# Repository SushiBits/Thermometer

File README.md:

# Thermocople Terminal

This is a thermocouple thermometer. Its USB link allows you to connect it to a
computer or a Raspberry Pi to log its output data.

For the matching firmware project, please visit [here](https://github.com/SushiBits/Thermocouple-firmware).

## License and more

This is open source hardware under [3-clause BSD license](LICENSE.md). You are
encouraged to modify and provide feedback.

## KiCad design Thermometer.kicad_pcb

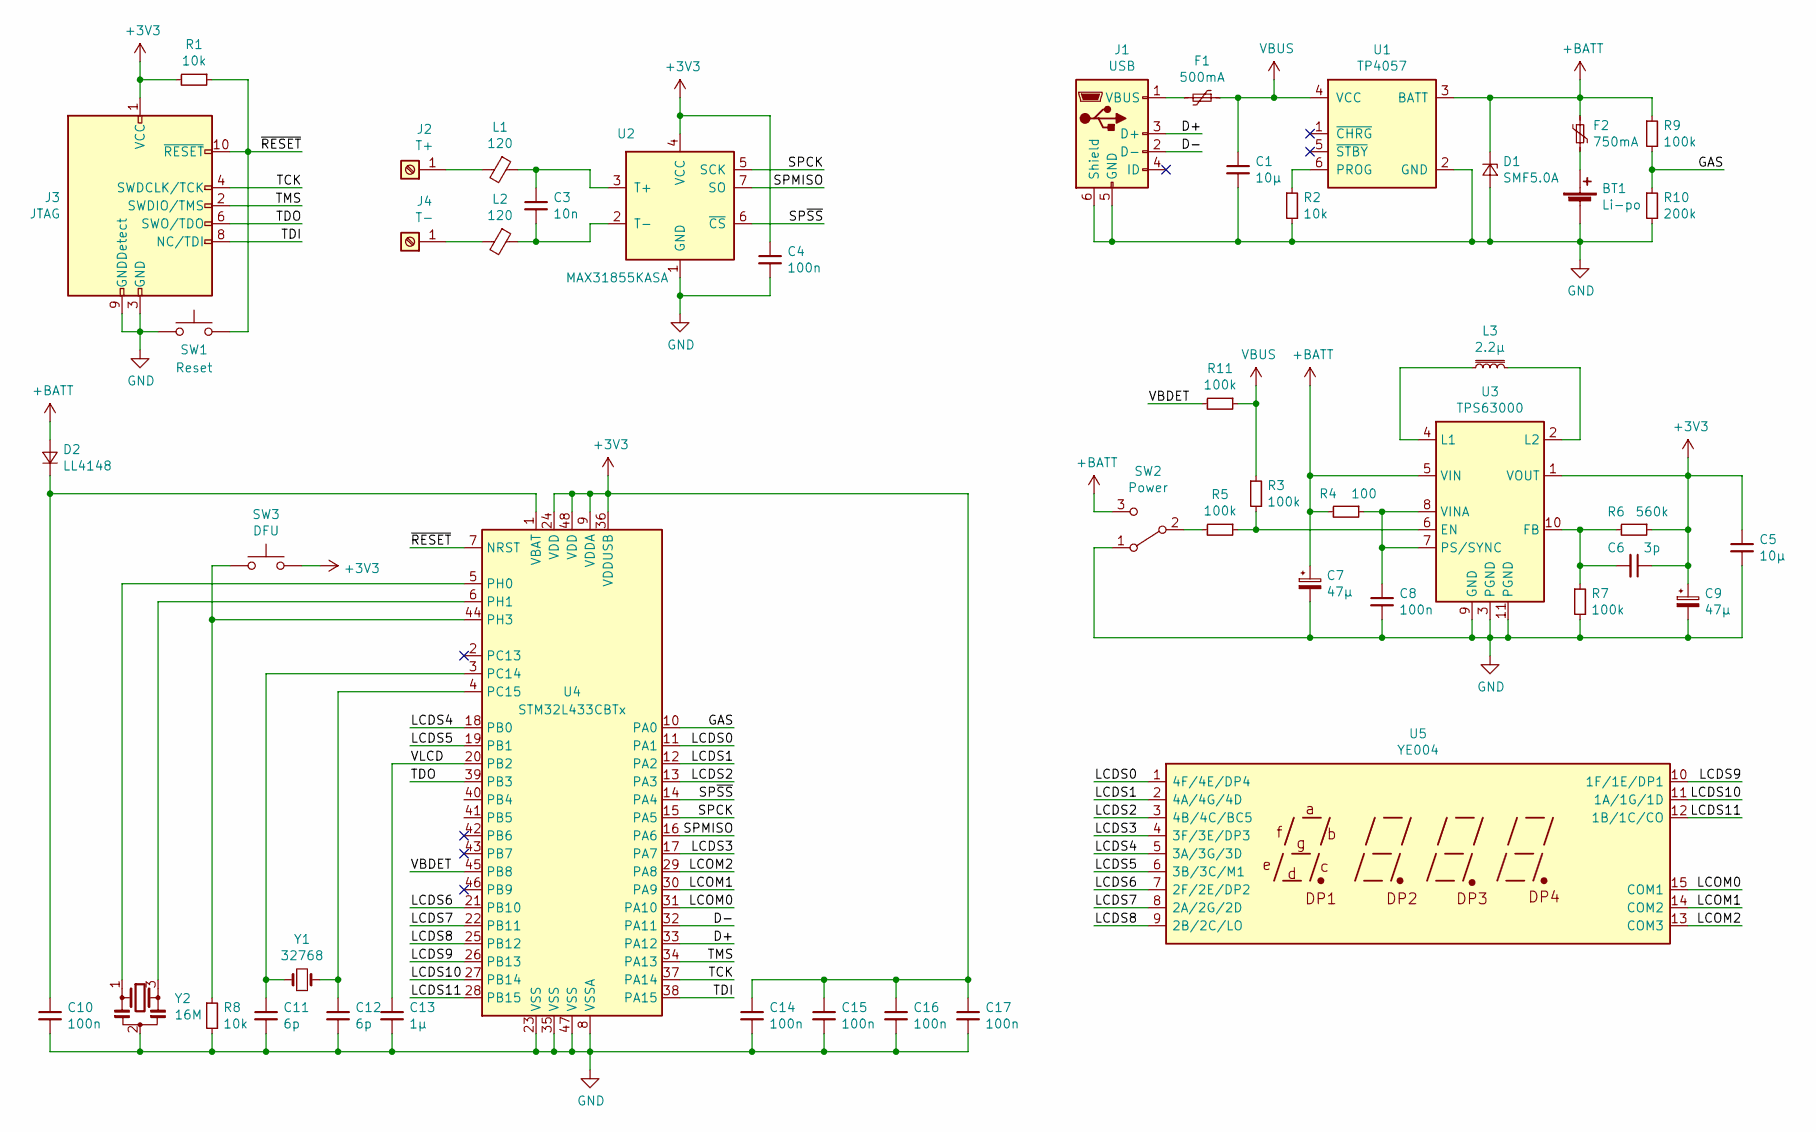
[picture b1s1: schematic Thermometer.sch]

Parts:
BT1: Li-po; PinHeader_1x02_P1.27mm_Vertical
C1, C5: 10µ; C_0805_2012Metric_Pad1.15x1.40mm_HandSolder
C3: 10n; C_0603_1608Metric_Pad1.05x0.95mm_HandSolder
C4, C8, C10, C14, C15, C16, C17: 100n; C_0603_1608Metric_Pad1.05x0.95mm_HandSolder
C6: 3p; C_0603_1608Metric_Pad1.05x0.95mm_HandSolder
C7, C9: 47µ; CP_EIA-3528-12_Kemet-T_Pad1.50x2.35mm_HandSolder
C11, C12: 6p; C_0603_1608Metric_Pad1.05x0.95mm_HandSolder
C13: 1µ; C_0603_1608Metric_Pad1.05x0.95mm_HandSolder
D1: SMF5.0A; D_SOD-123F
D2: LL4148; D_SOD-123
F1: 500mA; Fuse_1812_4532Metric_Pad1.30x3.40mm_HandSolder
F2: 750mA; Fuse_0805_2012Metric_Pad1.15x1.40mm_HandSolder
J1: USB; USB_Micro-B_A01SB1x41B
J2: T+; TerminalBlock_PCB-7
J3: JTAG; PinHeader_2x05_P1.27mm_Vertical_SMD
J4: T-; TerminalBlock_PCB-7
L1, L2: 120; L_0603_1608Metric_Pad1.05x0.95mm_HandSolder
L3: 2.2µ; L_Taiyo-Yuden_NR-20xx_HandSoldering
R1, R2, R8: 10k; R_0603_1608Metric_Pad1.05x0.95mm_HandSolder
R3, R5, R7, R9, R11: 100k; R_0603_1608Metric_Pad1.05x0.95mm_HandSolder
R4: 100; R_0603_1608Metric_Pad1.05x0.95mm_HandSolder
R6: 560k; R_0603_1608Metric_Pad1.05x0.95mm_HandSolder
R10: 200k; R_0603_1608Metric_Pad1.05x0.95mm_HandSolder
SW1: Reset; SW_SPST_FSMSM
SW2: Power; K3-1260D-L1
SW3: DFU; SW_SPST_FSMSM
U1: TP4057; SOT-23-6
U2: MAX31855KASA; SOIC-8_3.9x4.9mm_P1.27mm
U3: TPS63000; Texas_VSON-10-1EP_3x3mm
U4: STM32L433CBTx; LQFP-48_7x7mm_P0.5mm
U5: YE004
Y1: 32768; Crystal_SMD_3215-2Pin_3.2x1.5mm
Y2: 16M; Resonator_SMD_muRata_CSTxExxV-3Pin_3.0x1.1mm_HandSoldering

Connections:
+3V3: C4.1, C5.1, C6.1, C9.1, C14.1, C15.1, C16.1, C17.1, J3.1 (VCC), R1.2, R6.1, SW3.2, U2.4 (VCC), U3.1 (VOUT), U4.9 (VDDA), U4.24 (VDD), U4.36 (VDDUSB), U4.48 (VDD)
+BATT: C7.1, D1.1 (K), D2.2 (A), F2.1, R4.2, R9.1, SW2.3 (C), U1.3 (BATT), U3.5 (VIN)
/D+: J1.3 (D+), U4.33 (PA12)
/D-: J1.2 (D-), U4.32 (PA11)
/GAS: R9.2, R10.1, U4.10 (PA0)
/LCDS0: U4.11 (PA1), U5.1 (4F/4E/DP4)
/LCDS1: U4.12 (PA2), U5.2 (4A/4G/4D)
/LCDS2: U4.13 (PA3), U5.3 (4B/4C/BC5)
/LCDS3: U4.17 (PA7), U5.4 (3F/3E/DP3)
/LCDS4: U4.18 (PB0), U5.5 (3A/3G/3D)
/LCDS5: U4.19 (PB1), U5.6 (3B/3C/M1)
/LCDS6: U4.21 (PB10), U5.7 (2F/2E/DP2)
/LCDS7: U4.22 (PB11), U5.8 (2A/2G/2D)
/LCDS8: U4.25 (PB12), U5.9 (2B/2C/LO)
/LCDS9: U4.26 (PB13), U5.10 (1F/1E/DP1)
/LCDS10: U4.27 (PB14), U5.11 (1A/1G/1D)
/LCDS11: U4.28 (PB15), U5.12 (1B/1C/CO)
/LCOM0: U4.31 (PA10), U5.15 (COM1)
/LCOM1: U4.30 (PA9), U5.14 (COM2)
/LCOM2: U4.29 (PA8), U5.13 (COM3)
/SPCK: U2.5 (SCK), U4.15 (PA5)
/SPMISO: U2.7 (SO), U4.16 (PA6)
/SP~SS: U2.6 (~CS~), U4.14 (PA4)
/TCK: J3.4 (SWDCLK/TCK), U4.37 (PA14)
/TDI: J3.8 (NC/TDI), U4.38 (PA15)
/TDO: J3.6 (SWO/TDO), U4.39 (PB3)
/TMS: J3.2 (SWDIO/TMS), U4.34 (PA13)
/VBDET: R11.2, U4.45 (PB8)
/VLCD: C13.1, U4.20 (PB2)
/~RESET: J3.10 (~RESET~), R1.1, SW1.2, U4.7 (NRST)
GND: BT1.2 (-), C1.2, C4.2, C5.2, C7.2, C8.2, C9.2, C10.2, C11.2, C12.2, C13.2, C14.2, C15.2, C16.2, C17.2, D1.2 (A), J1.5 (GND), J1.6 (Shield), J3.3 (GND), J3.5 (GND), J3.9 (GNDDetect), R2.2, R7.2, R8.2, R10.2, SW1.1, SW2.1 (A), U1.2 (GND), U2.1 (GND), U3.3 (PGND), U3.9 (GND), U3.11 (PGND), U4.8 (VSSA), U4.23 (VSS), U4.35 (VSS), U4.47 (VSS), Y2.2
unnamed: BT1.1 (+), F2.2
unnamed: C3.1, L1.1, U2.3 (T+)
unnamed: C3.2, L2.1, U2.2 (T-)
unnamed: C6.2, R6.2, R7.1, U3.10 (FB)
unnamed: C8.1, R4.1, U3.7 (PS/SYNC), U3.8 (VINA)
unnamed: C10.1, D2.1 (K), U4.1 (VBAT)
unnamed: C11.1, U4.3 (PC14), Y1.1
unnamed: C12.1, U4.4 (PC15), Y1.2
unnamed: F1.2, J1.1 (VBUS)
unnamed: J2.1, L1.2
unnamed: J4.1, L2.2
unnamed: L3.1, U3.4 (L1)
unnamed: L3.2, U3.2 (L2)
unnamed: R2.1, U1.6 (PROG)
unnamed: R3.2, R5.1, U3.6 (EN)
unnamed: R5.2, SW2.2 (B)
unnamed: R8.1, SW3.1, U4.44 (PH3)
unnamed: U4.5 (PH0), Y2.1
unnamed: U4.6 (PH1), Y2.3
VBUS: C1.1, F1.1, R3.1, R11.1, U1.4 (VCC)

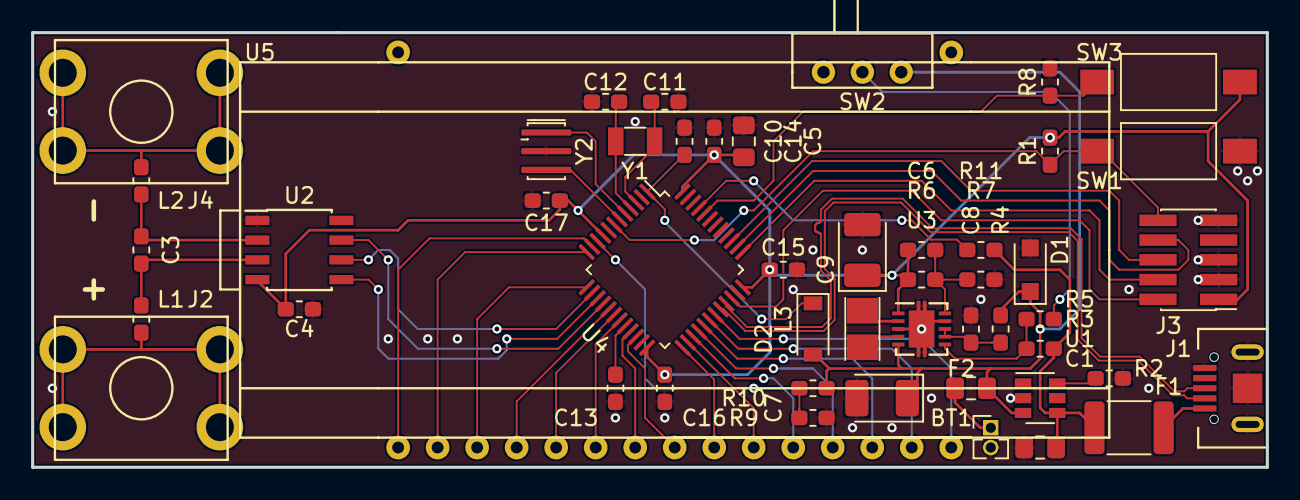
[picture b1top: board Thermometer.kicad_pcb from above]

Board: 2 copper layers, 79.4 x 27.9 mm, 49 parts (0 on the bottom side), 51 nets.

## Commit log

2019-03-19 Initial commit.
2019-03-19 Committing a previously unreleased project.
2019-03-19 Renaming the project.
2019-03-19 Adding descriptions.

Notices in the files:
Thermometer.kicad_pcb:
Copyright © 2018 Max Chan
